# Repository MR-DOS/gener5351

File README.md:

# gener5351
This is a simple 3-channel clock generator for frequencies up to 200 MHz with Si5351 PLL.

## HW
Currently, the HW part consists of the Si5351 conected to 3 edge SMA connectors, 6 buttons, 128x64 OLED and STM32F030F4P ARM Cortex M0 microcontroller. The board is powered from mini USB connector.

## SW
The software is currently being written and is not ready for being used. The SW is written in C and has SW4STM32 project format.

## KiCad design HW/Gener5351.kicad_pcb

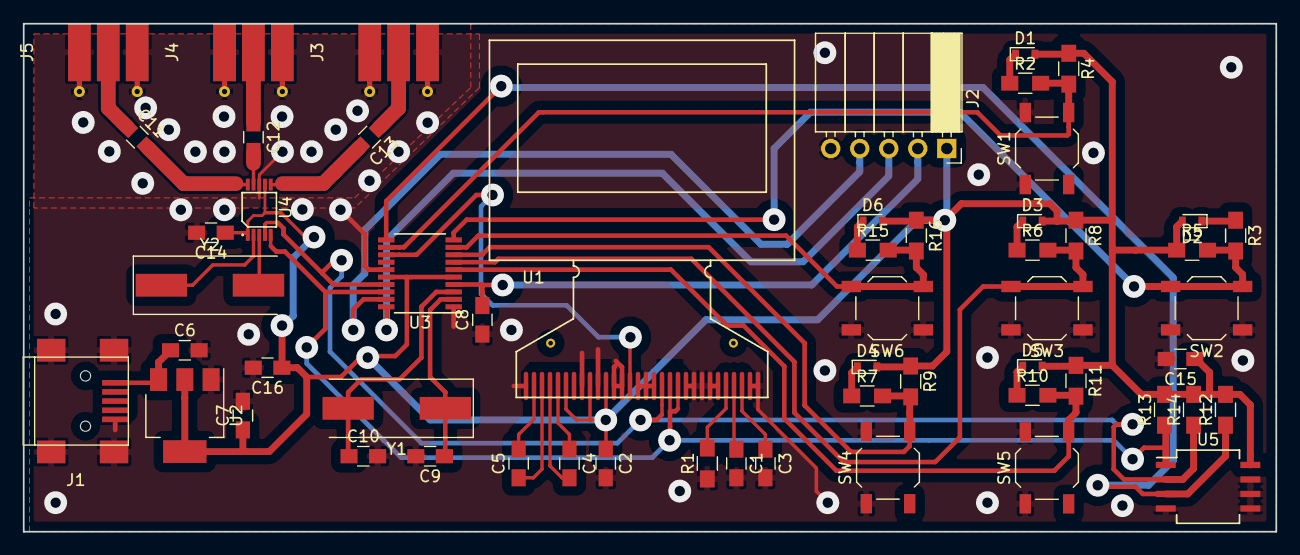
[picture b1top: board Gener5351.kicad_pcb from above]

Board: 2 copper layers, 109.6 x 44.5 mm, 56 parts (0 on the bottom side), 39 nets.

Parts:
C1: 4u7; C_0805_HandSoldering
C2, C3, C6: 2u2; C_0805_HandSoldering
C4, C5: 1u; C_0805_HandSoldering
C7, C11, C12, C13: 100n; C_0805_HandSoldering
C8: 220p; C_0805_HandSoldering
C9, C10: 15p; C_0805_HandSoldering
C14, C15, C16: 1n; C_0805_HandSoldering
D1, D2, D3, D4, D5, D6: LED_GRN; D_0603
J1: USB_OTG; USB_Mini-B
J2: Conn_01x05_Female; Socket_Strip_Angled_1x05_Pitch2.54mm
J3, J4, J5: Conn_Coaxial; Molex_SMA_Jack_Edge_Mount_Chinese
R1: 330K; R_0805_HandSoldering
R2, R3, R6, R7, R10, R15: 330; R_0805_HandSoldering
R4, R5, R8, R9, R11, R16: 10K; R_0805_HandSoldering
R12, R13, R14: 3K3; R_0805_HandSoldering
SW1, SW2, SW3, SW4, SW5, SW6: SW_SPST; SW_SPST_TL3342
U1: UG-2864KSWEG01
U2: AMS1117-3.3; SOT-223-3_TabPin2
U3: STM32F030F4P6; TSSOP-20_4.4x6.5mm_Pitch0.65mm
U4: Si5351A; MSOP-10
U5: LM75; SO-8_5.3x6.2mm_Pitch1.27mm
Y1: 8 MHz; Crystal_SMD_HC49-SD
Y2: 25 MHz; Crystal_SMD_HC49-SD

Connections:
/3V3: C2.1, C7.1, C14.1, C15.1, C16.1, D1.2, D2.2, D3.2, D4.2, D5.2, D6.2, J2.1, R4.1, R5.1, R8.1, R9.1, R11.1, R12.2, R13.2, R14.2, R16.1, U1.6, U1.9, U1.11, U2.2, U3.5, U3.16, U4.1, U4.7, U5.8
/BTN0: R2.2, R4.2, SW1.2, U3.12
/BTN1: R6.2, R8.2, SW3.2, U3.7
/BTN2: R10.2, R11.2, SW5.2, U3.6
/BTN3: R3.2, R5.2, SW2.2, U3.10
/BTN4: R7.2, R9.2, SW4.2, U3.8
/BTN5: R15.2, R16.2, SW6.2, U3.9
/OS: R12.1, U3.11, U5.3
/SCL: R14.1, U1.18, U3.17, U4.4, U5.2
/SDA: R13.1, U1.19, U1.20, U3.18, U4.5, U5.1
/SWCLK: J2.3, U3.20
/SWDIO: J2.4, U3.19
/XI: C9.1, U3.2, Y1.1
/XO: C10.1, U3.3, Y1.2
/~OLED_RESET: U1.14, U3.13
/~RST: C8.2, J2.2, U3.4
GND: C1.2, C2.2, C3.2, C6.2, C7.2, C8.1, C9.2, C10.2, C14.2, C15.2, C16.2, J1.5, J1.6, J2.5, J3.2, J4.2, J5.2, R1.1, SW1.1, SW2.1, SW3.1, SW4.1, SW5.1, SW6.1, U1.1, U1.8, U1.10, U1.12, U1.13, U1.15, U1.16, U1.17, U1.21, U1.22, U1.23, U1.24, U1.25, U1.29, U1.30, U2.1, U3.1, U3.15, U4.8, U5.4, U5.5, U5.6, U5.7
unnamed: C1.1, U1.27
unnamed: C3.1, U1.28
unnamed: C4.1, U1.5
unnamed: C4.2, U1.4
unnamed: C5.1, U1.3
unnamed: C5.2, U1.2
unnamed: C6.1, J1.1, U2.3
unnamed: C11.1, J5.1
unnamed: C11.2, U4.10
unnamed: C12.1, J4.1
unnamed: C12.2, U4.9
unnamed: C13.1, J3.1
unnamed: C13.2, U4.6
unnamed: D1.1, R2.1
unnamed: D2.1, R3.1
unnamed: D3.1, R6.1
unnamed: D4.1, R7.1
unnamed: D5.1, R10.1
unnamed: D6.1, R15.1
unnamed: R1.2, U1.26
unnamed: U4.2, Y2.1
unnamed: U4.3, Y2.2

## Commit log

2018-01-04 Gener5351 HW initial commit - stable version 001
2018-01-04 HW version 001 readme update
2021-11-23 Create LICENSE
    Added GPLv3 license
